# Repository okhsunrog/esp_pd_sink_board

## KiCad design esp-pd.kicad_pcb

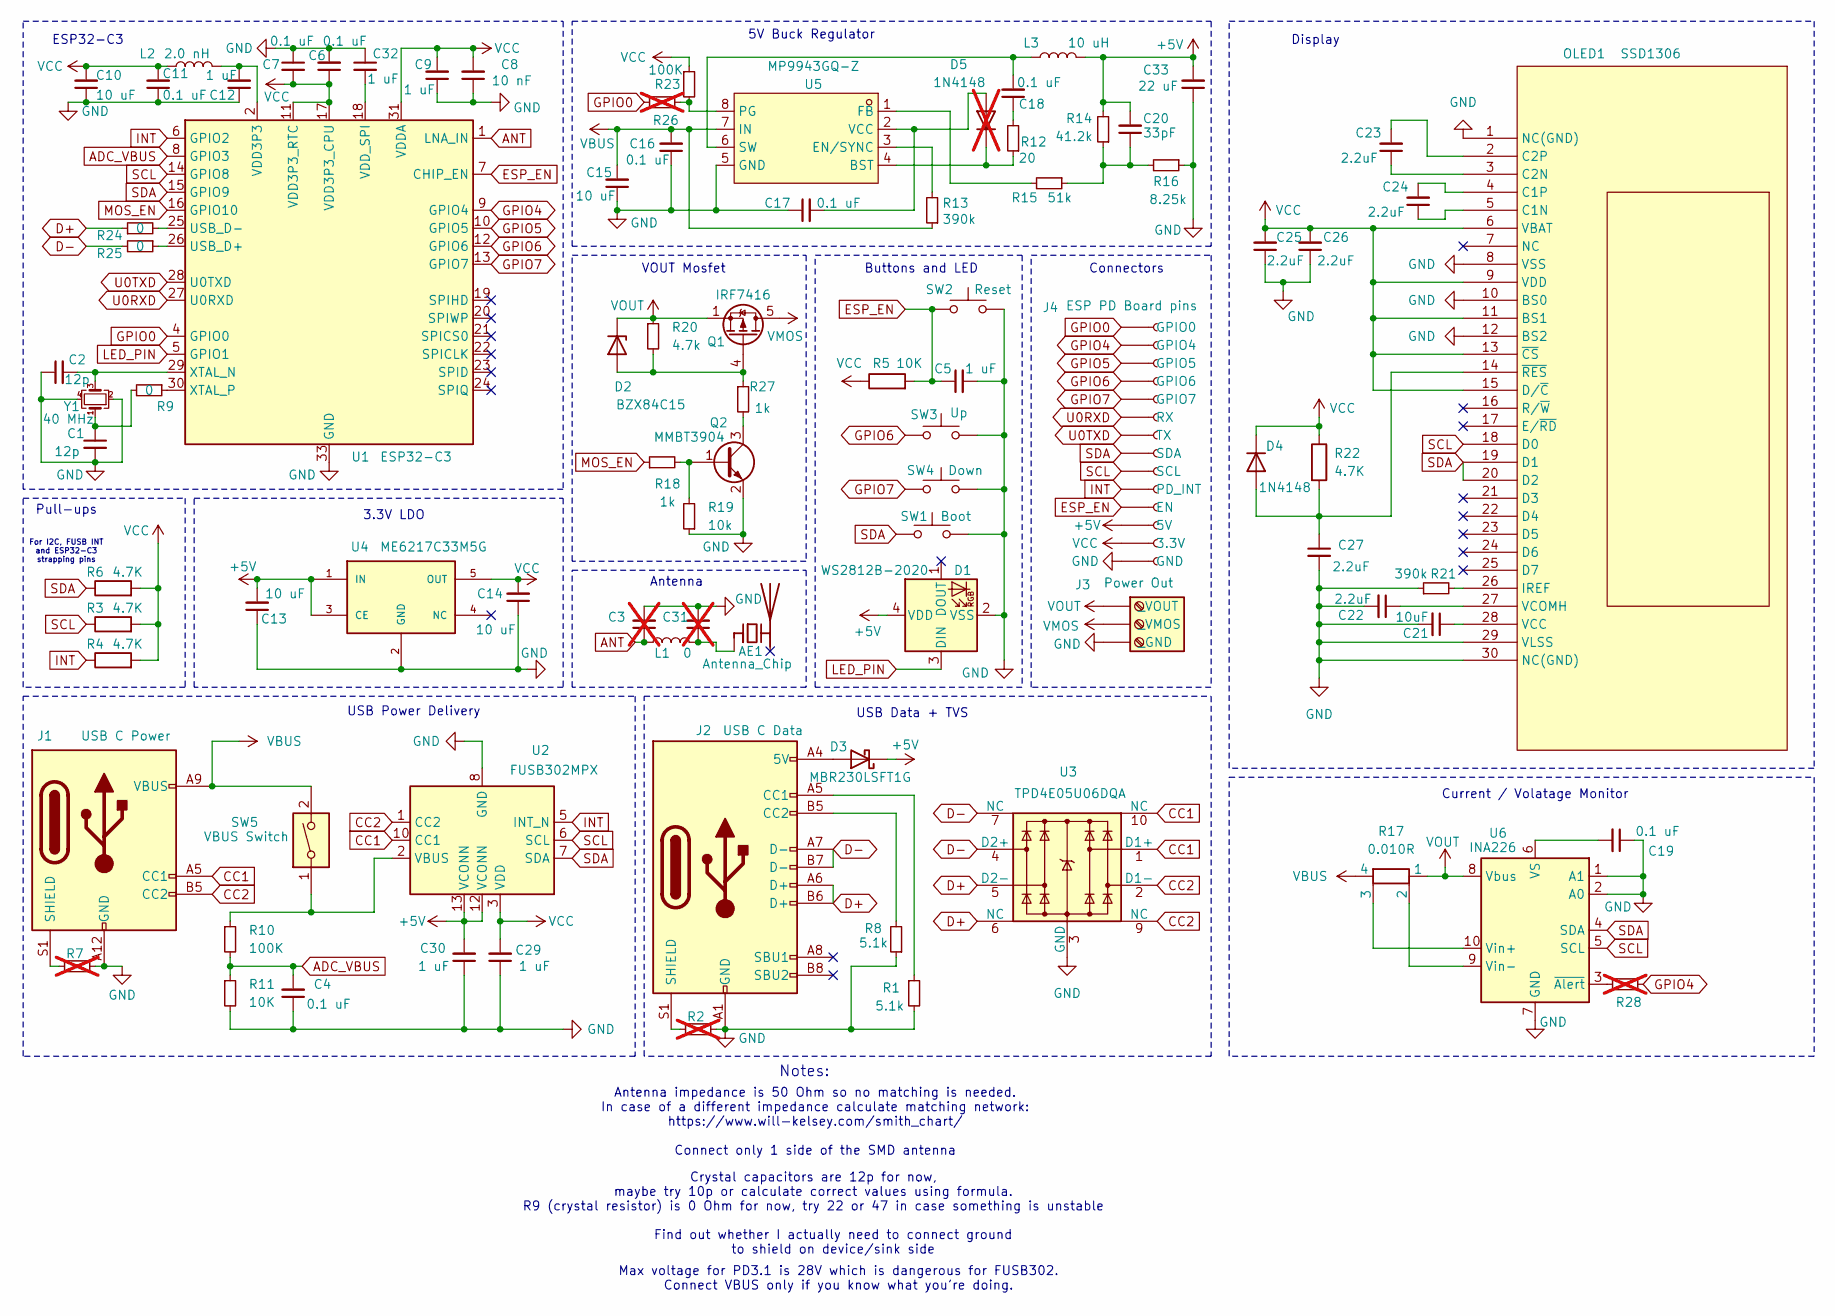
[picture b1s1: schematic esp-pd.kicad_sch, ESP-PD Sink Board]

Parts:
AE1: Antenna_Chip; Johanson_2450AT18x100
C1, C2: 12p; C_0402_1005Metric
C3, C31: C_0402_1005Metric; not fitted
C4, C6, C7, C11, C16, C17, C18, C19: 0.1 uF; C_0402_1005Metric
C5, C9, C12, C29, C30, C32: 1 uF; C_0402_1005Metric
C8: 10 nF; C_0402_1005Metric
C10, C13, C14: 10 uF; C_0603_1608Metric
C15: 10 uF; C_1210_3225Metric
C20: 33pF; C_0402_1005Metric
C21: 10uF; C_0402_1005Metric_Pad0.74x0.62mm_HandSolder
C22, C23, C24, C25, C26, C27: 2.2uF; C_0402_1005Metric_Pad0.74x0.62mm_HandSolder
C33: 22 uF; C_0603_1608Metric
D1: WS2812B-2020; LED_WS2812B-2020_PLCC4_2.0x2.0mm
D2: BZX84C15; SOT-23
D3: MBR230LSFT1G; SOD-123F
D4: 1N4148; D_SOD-523
D5: 1N4148; D_SOD-523; not fitted
J1: USB C Power; USB_C_Receptacle_GCT_USB4125-xx-x-0190_6P_TopMnt_Horizontal
J2: USB C Data; USB_C_Receptacle_GCT_USB4105-xx-A_16P_TopMnt_Horizontal
J3: Power Out; TerminalBlock_bornier-3_P5.08mm
J4: ESP PD Board pins; PinHeader_1x14_P2.54mm_Vertical
L1: 0; L_0402_1005Metric
L2: 2.0 nH; L_0402_1005Metric
L3: 10 uH; L_Chilisin_BMRB00060650
OLED1: SSD1306
Q1: IRF7416; SOP-8_3.76x4.96mm_P1.27mm
Q2: MMBT3904; SOT-23
R1, R8: 5.1k; R_0402_1005Metric
R2, R7: R_0402_1005Metric; not fitted
R3, R4, R6: 4.7K; R_0402_1005Metric
R5, R11: 10K; R_0402_1005Metric
R9, R24, R25: 0; R_0402_1005Metric
R10, R23: 100K; R_0402_1005Metric
R12: 20; R_0402_1005Metric
R13: 390k; R_0402_1005Metric
R14: 41.2k; R_0402_1005Metric
R15: 51k; R_0402_1005Metric
R16: 8.25k; R_0402_1005Metric
R17: 0.010R; R_Shunt_Vishay_WSK2512_6332Metric_new
R18, R27: 1k; R_0402_1005Metric
R19: 10k; R_0402_1005Metric
R20: 4.7k; R_0402_1005Metric
R21: 390k; R_0402_1005Metric_Pad0.72x0.64mm_HandSolder
R22: 4.7K; R_0402_1005Metric_Pad0.72x0.64mm_HandSolder
R26, R28: 0; R_0402_1005Metric; not fitted
SW1: Boot; Button SMD 3x4
SW2: Reset; Button SMD 3x4
SW3: Up; Button SMD 3x4
SW4: Down; Button SMD 3x4
SW5: VBUS Switch; SW_DIP_SPSTx01_Slide_9.78x4.72mm_W7.62mm_P2.54mm
U1: ESP32-C3; QFN-32-1EP_5x5mm_P0.5mm_EP3.7x3.7mm
U2: FUSB302MPX; WQFN-14-1EP_2.5x2.5mm_P0.5mm_EP1.45x1.45mm
U3: TPD4E05U06DQA; USON-10_2.5x1.0mm_P0.5mm
U4: ME6217C33M5G; SOT23-5; M_PART_NUMBER ME6217C33M5G
U5: MP9943GQ-Z; QFN-8_L3.0-W3.0-P0.65-BL; LCSC Part C477821
U6: INA226; VSSOP-10_3x3mm_P0.5mm
Y1: 40 MHz; Crystal_SMD_3225-4Pin_3.2x2.5mm

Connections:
+5V: C13.2, C20.2, C30.2, C33.2, D1.4 (VDD), D3.2 (K), J4.12 (5V), L3.2, R14.2, U2.12 (VCONN), U2.13 (VCONN), U4.1 (IN), U4.3 (CE)
ADC_VBUS: C4.2, R10.2, R11.1, U1.8 (GPIO3)
ANT: C3.1, L1.1, U1.1 (LNA_IN)
CC1: J1.A5 (CC1), U2.10 (CC1), U2.11 (CC1), U3.1 (D1+), U3.10 (NC)
CC2: J1.B5 (CC2), U2.1 (CC2), U2.14 (CC2), U3.2 (D1-), U3.9 (NC)
D+: J2.A6 (D+), J2.B6 (D+), R24.1, U3.5 (D2-), U3.6 (NC)
D-: J2.A7 (D-), J2.B7 (D-), R25.2, U3.4 (D2+), U3.7 (NC)
ESP_EN: C5.1, J4.11 (EN), R5.2, SW2.1, U1.7 (CHIP_EN)
GND: C1.2, C2.1, C3.2, C4.1, C5.2, C6.2, C7.1, C8.1, C9.1, C10.1, C11.1, C12.1, C13.1, C14.1, C15.1, C16.1, C17.1, C19.1, C21.2, C22.2, C25.1, C26.1, C27.2, C29.1, C30.1, C31.2, C32.1, C33.1, D1.2 (VSS), J1.A12 (GND), J1.B12 (GND), J2.A1 (GND), J2.A12 (GND), J2.B1 (GND), J2.B12 (GND), J3.3 (_GND), J4.14 (GND), OLED1.1 (NC(GND)), OLED1.8 (VSS), OLED1.10 (BS0), OLED1.12 (BS2), OLED1.29 (VLSS), OLED1.30 (NC(GND)), Q2.2 (E), R1.2, R2.2, R7.2, R8.1, R11.2, R16.1, R19.1, R21.1, SW1.2, SW2.2, SW3.2, SW4.2, U1.33 (GND), U2.8 (GND), U2.9 (GND), U2.15 (GND), U3.3 (GND), U3.8 (GND), U4.2 (GND), U5.5 (GND), U6.1 (A1), U6.2 (A0), U6.7 (GND), Y1.2, Y1.4
GPIO0: J4.1 (GPIO0), R26.2, U1.4 (GPIO0)
GPIO4: J4.2 (GPIO4), R28.1, U1.9 (GPIO4)
GPIO5: J4.3 (GPIO5), U1.10 (GPIO5)
GPIO6: J4.4 (GPIO6), SW3.1, U1.12 (GPIO6)
GPIO7: J4.5 (GPIO7), SW4.1, U1.13 (GPIO7)
INT: J4.10 (PD_INT), R4.1, U1.6 (GPIO2), U2.5 (INT_N)
LED_PIN: D1.3 (DIN), U1.5 (GPIO1)
MOS_EN: R18.1, U1.16 (GPIO10)
unnamed: AE1.1 (FEED), C31.1, L1.2
unnamed: C1.1, R9.2, Y1.1
unnamed: C12.2, L2.2, U1.2 (VDD3P3), U1.3 (VDD3P3)
unnamed: C18.1, R12.2
unnamed: C20.1, R14.1, R15.1, R16.2
unnamed: D2.1 (A), Q1.4 (G), R20.2, R27.1
unnamed: D3.1 (A), J2.A4 (5V), J2.A9 (VBUS), J2.B4 (VBUS), J2.B9 (VBUS)
unnamed: C27.1, D4.2 (A), OLED1.14 (~RES), R22.2
unnamed: C17.2, D5.2 (A), U5.2 (VCC)
unnamed: D5.1 (K), R12.1, U5.4 (BST)
unnamed: J1.S1 (SHIELD), R7.1
unnamed: J2.A5 (CC1), R1.1
unnamed: J2.B5 (CC2), R8.2
unnamed: J2.S1 (SHIELD), R2.1
unnamed: C24.1, OLED1.5 (C1N)
unnamed: C24.2, OLED1.4 (C1P)
unnamed: C23.1, OLED1.3 (C2N)
unnamed: C23.2, OLED1.2 (C2P)
unnamed: OLED1.26 (IREF), R21.2
unnamed: C21.1, OLED1.28 (VCC)
unnamed: C22.1, OLED1.27 (VCOMH)
unnamed: Q2.1 (B), R18.2, R19.2
unnamed: Q2.3 (C), R27.2
unnamed: R25.1, U1.26 (USB_D+)
unnamed: R24.2, U1.25 (USB_D-)
unnamed: C32.2, U1.18 (VDD_SPI)
unnamed: C2.2, U1.29 (XTAL_N), Y1.3
unnamed: R9.1, U1.30 (XTAL_P)
unnamed: R10.1, SW5.1, U2.2 (VBUS)
unnamed: R13.2, U5.3 (EN/SYNC)
unnamed: R15.2, U5.1 (FB)
unnamed: R23.2, R26.1, U5.8 (PG)
unnamed: C18.2, L3.1, U5.6 (SW)
unnamed: C19.2, U6.6 (VS)
unnamed: R17.3, U6.10 (Vin+)
unnamed: R17.2, U6.9 (Vin-)
unnamed: R28.2, U6.3 (~Alert)
SCL: J4.9 (SCL), OLED1.18 (D0), R3.1, U1.14 (GPIO8), U2.6 (SCL), U6.5 (SCL)
SDA: J4.8 (SDA), OLED1.19 (D1), OLED1.20 (D2), R6.1, SW1.1, U1.15 (GPIO9), U2.7 (SDA), U6.4 (SDA)
U0RXD: J4.6 (RX), U1.27 (U0RXD)
U0TXD: J4.7 (TX), U1.28 (U0TXD)
VBUS: C15.2, C16.2, J1.A9 (VBUS), J1.B9 (VBUS), R13.1, R17.4, SW5.2, U5.7 (IN)
VCC: C6.1, C7.2, C8.2, C9.2, C10.2, C11.2, C14.2, C25.2, C26.2, C29.2, D4.1 (K), J4.13 (3.3V), L2.1, OLED1.6 (VBAT), OLED1.9 (VDD), OLED1.11 (BS1), OLED1.13 (~CS), OLED1.15 (D/~C), R3.2, R4.2, R5.1, R6.2, R22.1, R23.1, U1.11 (VDD3P3_RTC), U1.17 (VDD3P3_CPU), U1.31 (VDDA), U1.32 (VDDA), U2.3 (VDD), U2.4 (VDD), U4.5 (OUT)
VMOS: J3.2 (_VMOS), Q1.5 (D), Q1.6 (D), Q1.7 (D), Q1.8 (D)
VOUT: D2.3 (K), J3.1 (_VOUT), Q1.1 (S), Q1.2 (S), Q1.3 (S), R17.1, R20.1, U6.8 (Vbus)

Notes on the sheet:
Buttons and LED
Pull-ups
Find out whether I actually need to connect ground to shield on device/sink side
5V Buck Regulator
Crystal capacitors are 12p for now, maybe try 10p or calculate correct values using formula. R9 (crystal resistor) is 0 Ohm for now, try 22 or 47 in case something is unstable
Notes:
For I2C, FUSB INT and ESP32-C3 strapping pins
Current / Volatage Monitor
USB Data + TVS
Max voltage for PD3.1 is 28V which is dangerous for FUSB302. Connect VBUS only if you know what you're doing.
Antenna impedance is 50 Ohm so no matching is needed. In case of a different impedance calculate matching network: https://www.will-kelsey.com/smith_chart/ Connect only 1 side of the SMD antenna
VOUT Mosfet
3.3V LDO
Connectors
Display
ESP32-C3
USB Power Delivery
Antenna

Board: 4 copper layers, 88 parts (12 on the bottom side), 62 nets, no tracks yet.

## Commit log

2024-07-03 refactored
2024-07-03 added logos
2024-07-03 footprints partially assigned
2024-07-03 footprints assigned
2024-07-03 started PCB
2024-07-04 A4 format
2024-07-04 preparing to route PCB x1
2024-07-05 correct chip antenna footprint
2024-07-05 some eeschema parameters are changed
2024-07-05 edited footprints
2024-07-05 edited footprint for button
2024-07-06 added BST diode
2024-09-23 added INA226
